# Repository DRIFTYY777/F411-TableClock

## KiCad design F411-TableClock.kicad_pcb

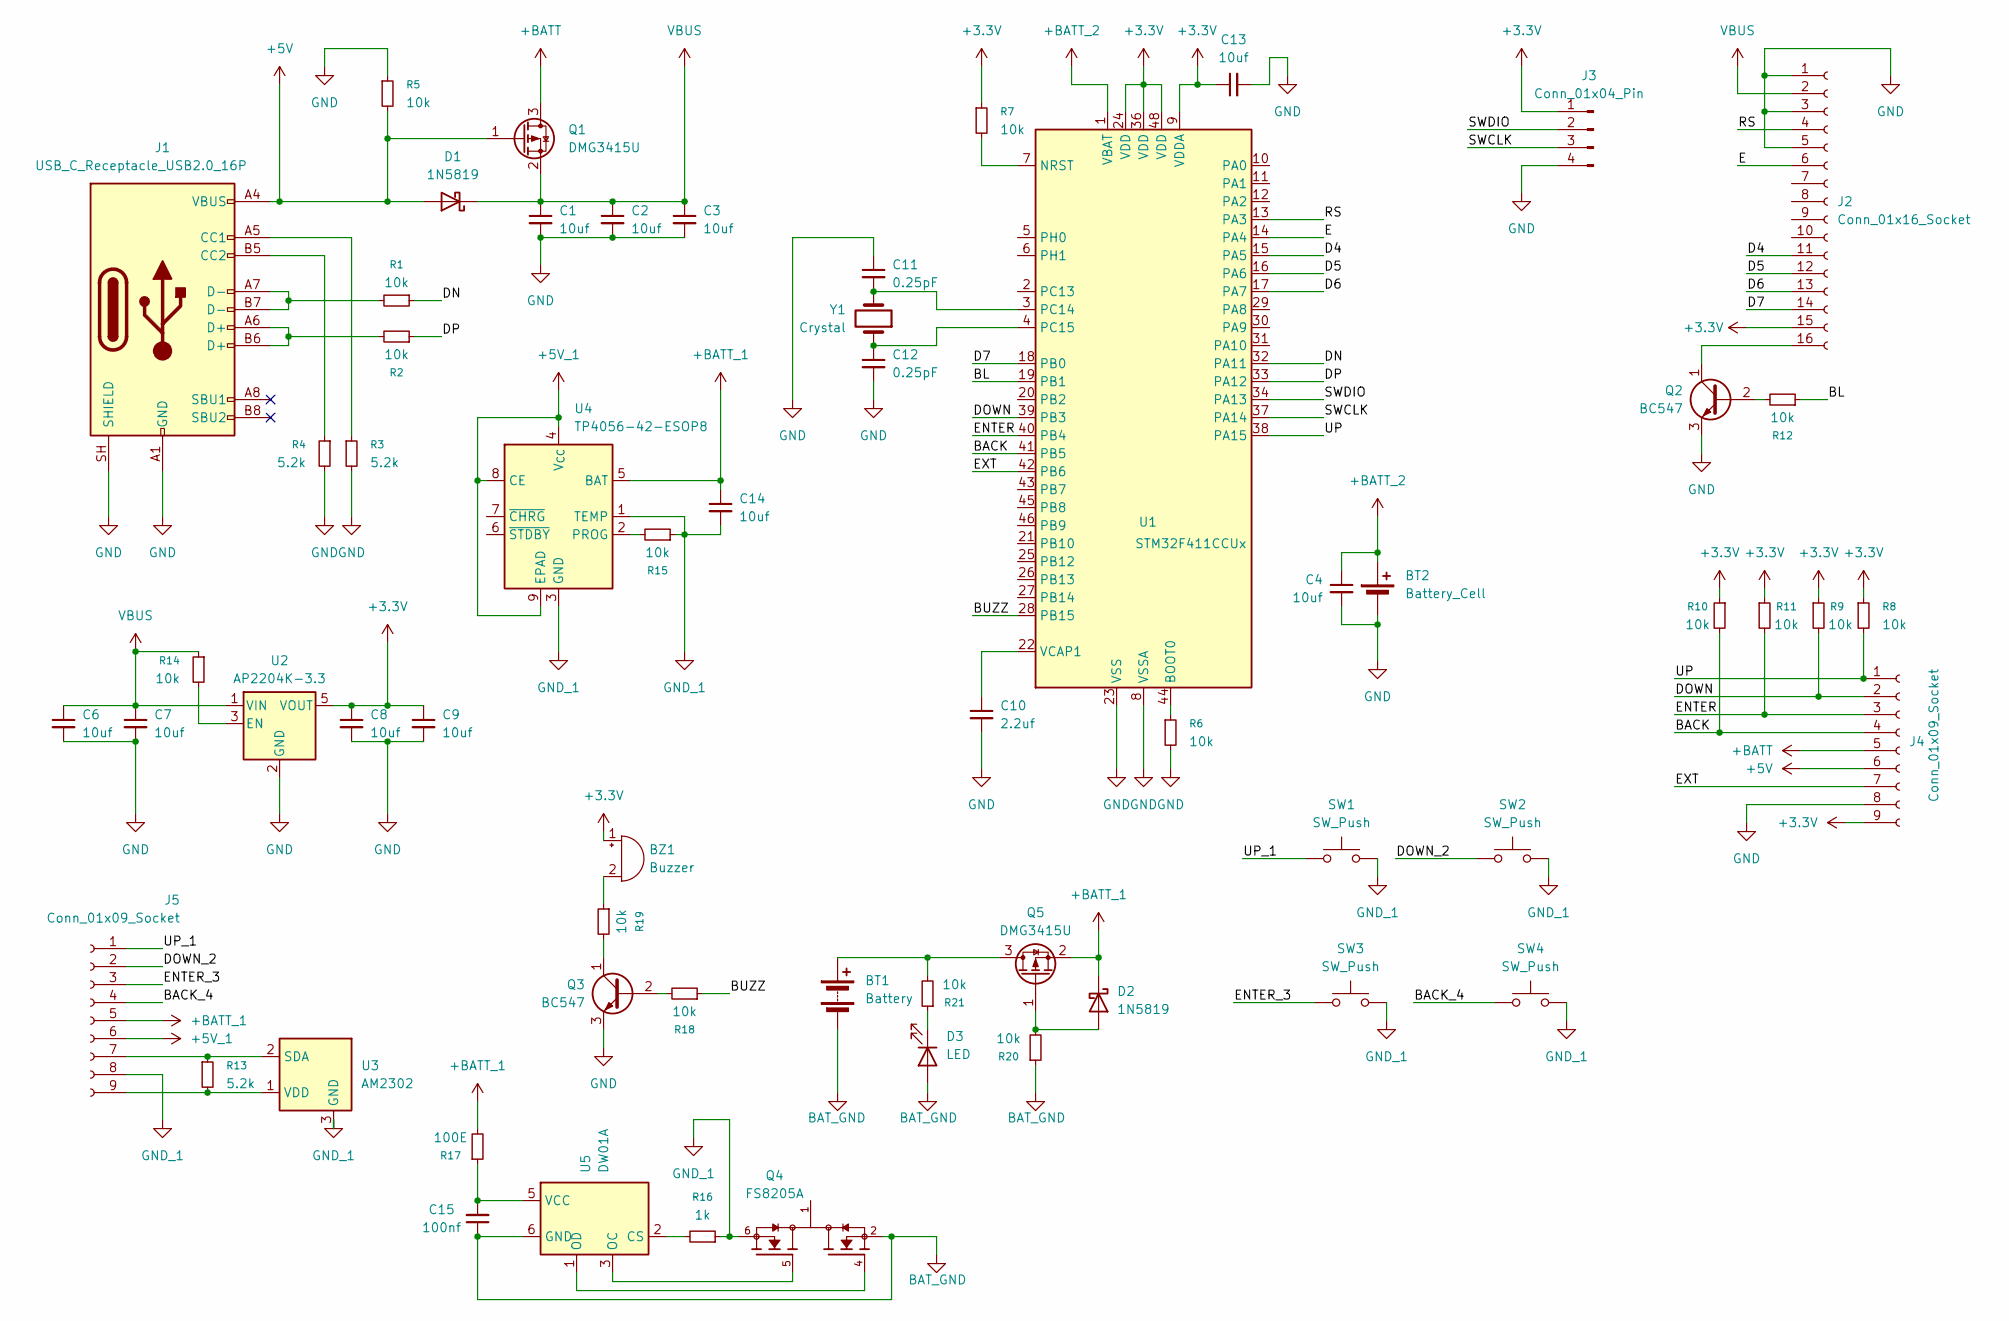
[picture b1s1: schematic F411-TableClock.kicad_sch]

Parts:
BT1: Battery; BatteryHolder_MPD_BK-18650-PC2
BT2: Battery_Cell; Battery_Panasonic_CR2032-HFN_Horizontal_CircularHoles
BZ1: Buzzer; Buzzer_12x9.5RM7.6
C1, C2, C3, C4, C6, C7, C8, C9, C13, C14: 10uf; C_0805_2012Metric
C10: 2.2uf; C_0805_2012Metric
C11, C12: 0.25pF; R_0805_2012Metric
C15: 100nf; C_0805_2012Metric
D1, D2: 1N5819; D_0805_2012Metric
D3: LED; LED_0805_2012Metric
J1: USB_C_Receptacle_USB2.0_16P; USB_C_Receptacle_GCT_USB4105-xx-A_16P_TopMnt_Horizontal
J2: Conn_01x16_Socket; PinSocket_1x16_P2.54mm_Vertical
J3: Conn_01x04_Pin; PinHeader_1x04_P2.54mm_Vertical
J4: Conn_01x09_Socket; PinSocket_1x09_P2.54mm_Vertical
J5: Conn_01x09_Socket; PinHeader_1x09_P2.54mm_Vertical
Q1, Q5: DMG3415U; SOT-23
Q2, Q3: BC547; TSOT-23
Q4: FS8205A; TSSOP-8_4.4x3mm_P0.65mm; PARTREV 1.7
R1, R2, R5, R6, R7, R8, R9, R10, R11, R12, R14, R15, R18, R19, R20, R21: 10k; R_0805_2012Metric
R3, R4, R13: 5.2k; R_0805_2012Metric
R16: 1k; R_0805_2012Metric
R17: 100E; R_0805_2012Metric
SW1, SW2, SW3, SW4: SW_Push; SW_SPST_TL3342
U1: STM32F411CCUx; QFN-48-1EP_7x7mm_P0.5mm_EP5.15x5.15mm
U2: AP2204K-3.3; SOT-23-5
U3: AM2302; ASAIR_AM2302_P2.54mm_Vertical
U4: TP4056-42-ESOP8; SOIC-8-1EP_3.9x4.9mm_P1.27mm_EP2.41x3.3mm_ThermalVias
U5: DW01A; SOT-23-6
Y1: Crystal; Crystal_AT310_D3.0mm_L10.0mm_Vertical

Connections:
+3.3V: BZ1.1 (+), C8.1, C9.1, C13.1, J2.15, J3.1, J4.9, R7.1, R8.1, R9.1, R10.1, R11.1, U1.9 (VDDA), U1.24 (VDD), U1.36 (VDD), U1.48 (VDD), U2.5 (VOUT)
+5V: D1.2 (A), J1.A4 (VBUS), J1.A9 (VBUS), J1.B4 (VBUS), J1.B9 (VBUS), J4.6, Q1.1 (G), R5.2
+5V_1: J5.6, U4.4 (V_{CC}), U4.8 (CE), U4.9 (EPAD)
+BATT: J4.5, Q1.3 (D)
+BATT_1: C14.1, D2.1 (K), J5.5, Q5.2 (S), R17.2, U4.5 (BAT)
+BATT_2: BT2.1 (+), C4.1, U1.1 (VBAT)
/BACK: J4.4, R10.2, U1.41 (PB5)
/BACK_4: J5.4, SW4.1
/BL: R12.1, U1.19 (PB1)
/BUZZ: R18.1, U1.28 (PB15)
/D4: J2.11, U1.15 (PA5)
/D5: J2.12, U1.16 (PA6)
/D6: J2.13, U1.17 (PA7)
/D7: J2.14, U1.18 (PB0)
/DN: R1.1, U1.32 (PA11)
/DOWN: J4.2, R9.2, U1.39 (PB3)
/DOWN_2: J5.2, SW2.1
/DP: R2.1, U1.33 (PA12)
/E: J2.6, U1.14 (PA4)
/ENTER: J4.3, R11.2, U1.40 (PB4)
/ENTER_3: J5.3, SW3.1
/EXT: J4.7, U1.42 (PB6)
/RS: J2.4, U1.13 (PA3)
/SWCLK: J3.3, U1.37 (PA14)
/SWDIO: J3.2, U1.34 (PA13)
/UP: J4.1, R8.2, U1.38 (PA15)
/UP_1: J5.1, SW1.1
BAT_GND: BT1.2 (-), C15.1, D3.2 (A), Q4.2, Q4.3, R20.1, U5.6 (GND)
GND: BT2.2 (-), C1.2, C2.2, C3.2, C4.2, C6.2, C7.2, C8.2, C9.2, C10.2, C11.1, C12.2, C13.2, J1.A1 (GND), J1.A12 (GND), J1.B1 (GND), J1.B12 (GND), J1.SH (SHIELD), J2.1, J2.3, J2.5, J3.4, J4.8, Q2.3 (E), Q3.3 (E), R3.2, R4.2, R5.1, R6.2, U1.8 (VSSA), U1.23 (VSS), U1.35 (VSS), U1.47 (VSS), U1.49 (VSS), U2.2 (GND)
GND_1: C14.2, J5.8, Q4.6, Q4.7, R15.1, R16.1, SW1.2, SW2.2, SW3.2, SW4.2, U3.3 (GND), U3.4 (GND), U4.1 (TEMP), U4.3 (GND)
unnamed: BT1.1 (+), Q5.3 (D), R21.2
unnamed: BZ1.2 (-), R19.1
unnamed: D2.2 (A), Q5.1 (G), R20.2
unnamed: D3.1 (K), R21.1
unnamed: J1.A5 (CC1), R3.1
unnamed: J1.B5 (CC2), R4.1
unnamed: J1.A6 (D+), J1.B6 (D+), R2.2
unnamed: J1.A7 (D-), J1.B7 (D-), R1.2
unnamed: J2.16, Q2.1 (C)
unnamed: J5.7, R13.1, U3.2 (SDA)
unnamed: J5.9, R13.2, U3.1 (VDD)
unnamed: Q2.2 (B), R12.2
unnamed: Q3.2 (B), R18.2
unnamed: Q3.1 (C), R19.2
unnamed: Q4.1, Q4.8
unnamed: R6.1, U1.44 (BOOT0)
unnamed: R7.2, U1.7 (NRST)
unnamed: C11.2, U1.3 (PC14), Y1.2
unnamed: C12.1, U1.4 (PC15), Y1.1
unnamed: C10.1, U1.22 (VCAP1)
unnamed: R14.2, U2.3 (EN)
unnamed: R15.2, U4.2 (PROG)
unnamed: R16.2, U5.2 (CS)
unnamed: Q4.5, U5.3 (OC)
unnamed: Q4.4, U5.1 (OD)
unnamed: C15.2, R17.1, U5.5 (VCC)
VBUS: C1.1, C2.1, C3.1, C6.1, C7.1, D1.1 (K), J2.2, Q1.2 (S), R14.1, U2.1 (VIN)

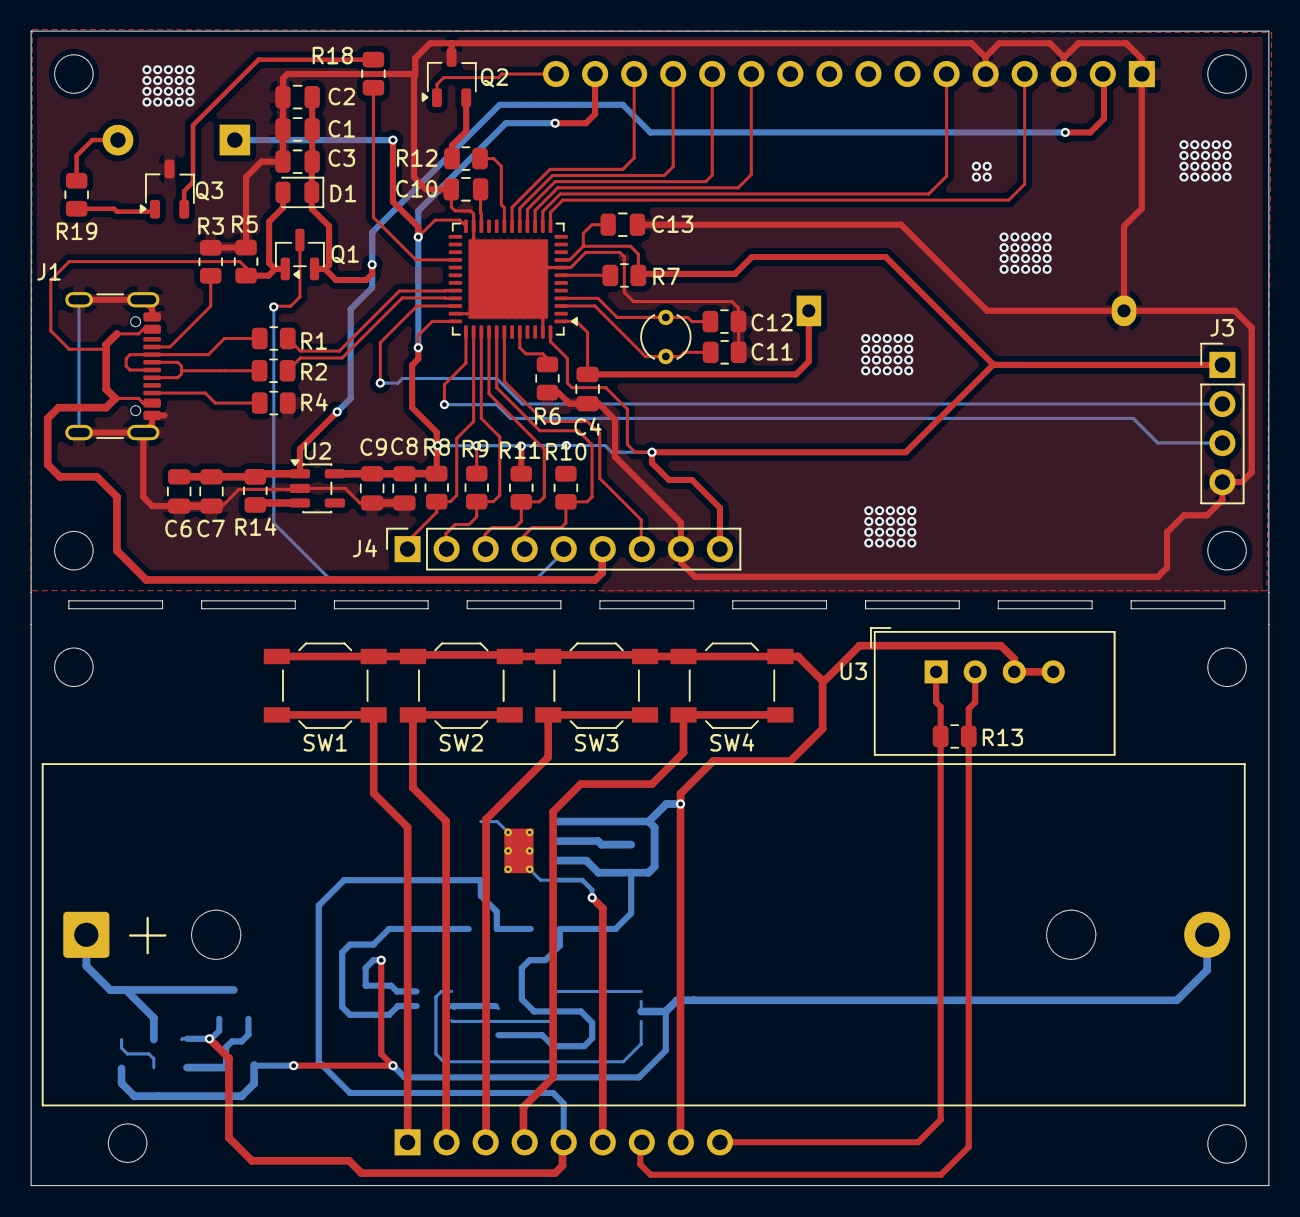
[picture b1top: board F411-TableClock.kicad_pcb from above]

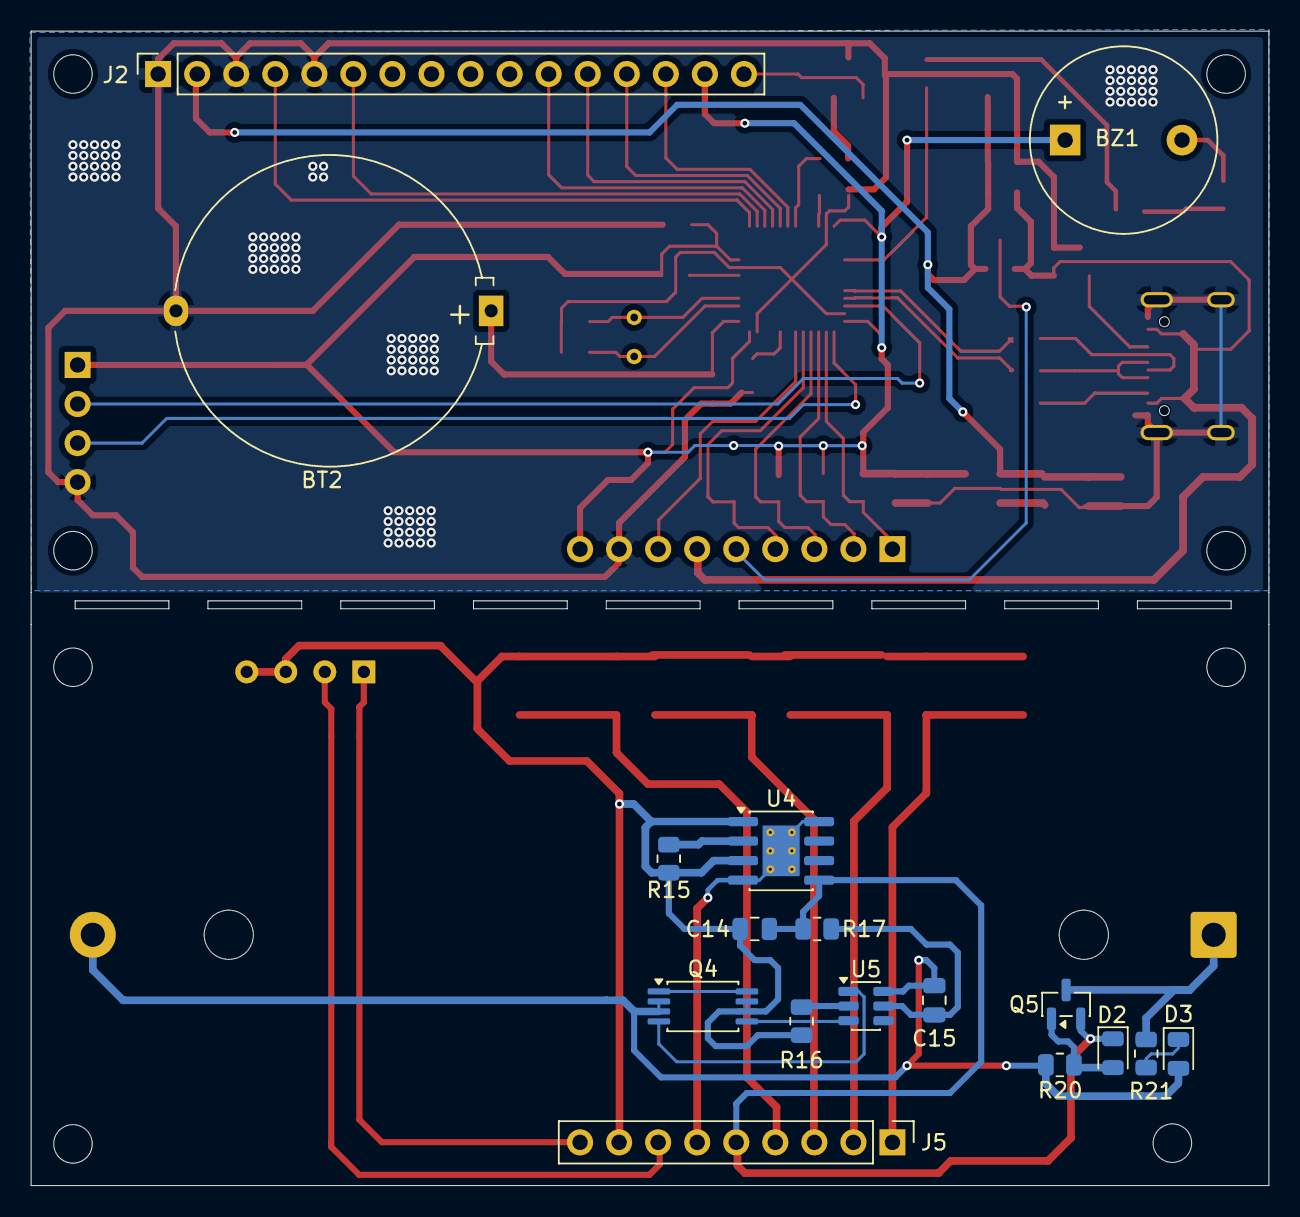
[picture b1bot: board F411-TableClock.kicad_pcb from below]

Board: 2 copper layers, 80.5 x 75.1 mm, 61 parts (17 on the bottom side), 57 nets.

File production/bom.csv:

Designator,Footprint,Quantity,Value,LCSC Part #
BT1,BatteryHolder_MPD_BK-18650-PC2,1,Battery,
BT2,Battery_Panasonic_CR2032-HFN_Horizontal_CircularHoles,1,Battery_Cell,
"C1, C13, C2, C3, C4, C5, C6, C7, C8, C9",0805,10,10uf,
C10,0805,1,2.2uf,
"C11, C12",0805,2,0.25pF,
D1,0805,1,1N5819,
J1,USB_C_Receptacle_GCT_USB4105-xx-A_16P_TopMnt_Horizontal,1,USB_C_Receptacle_USB2.0_16P,
J2,PinSocket_1x16_P2.54mm_Vertical,1,Conn_01x16_Socket,
J3,PinHeader_1x04_P2.54mm_Vertical,1,Conn_01x04_Pin,
J4,PinSocket_1x09_P2.54mm_Vertical,1,Conn_01x09_Socket,
J5,PinHeader_1x09_P2.54mm_Vertical,1,Conn_01x09_Socket,
Q1,SOT-23,1,DMG3415U,
Q2,TO-92L_Wide,1,BC547,
"R1, R10, R11, R12, R14, R2, R5, R6, R7, R8, R9",0805,11,10k,
"R13, R3, R4",0805,3,5.2k,
"SW1, SW2, SW3, SW4",SW_SPST_TL3342,4,SW_Push,
U1,QFN-48-1EP_7x7mm_P0.5mm_EP5.15x5.15mm,1,STM32F411CCUx,
U2,SOT-23-5,1,AP2204K-3.3,
U3,ASAIR_AM2302_P2.54mm_Vertical,1,AM2302,
Y1,Crystal_AT310_D3.0mm_L10.0mm_Vertical,1,Crystal,

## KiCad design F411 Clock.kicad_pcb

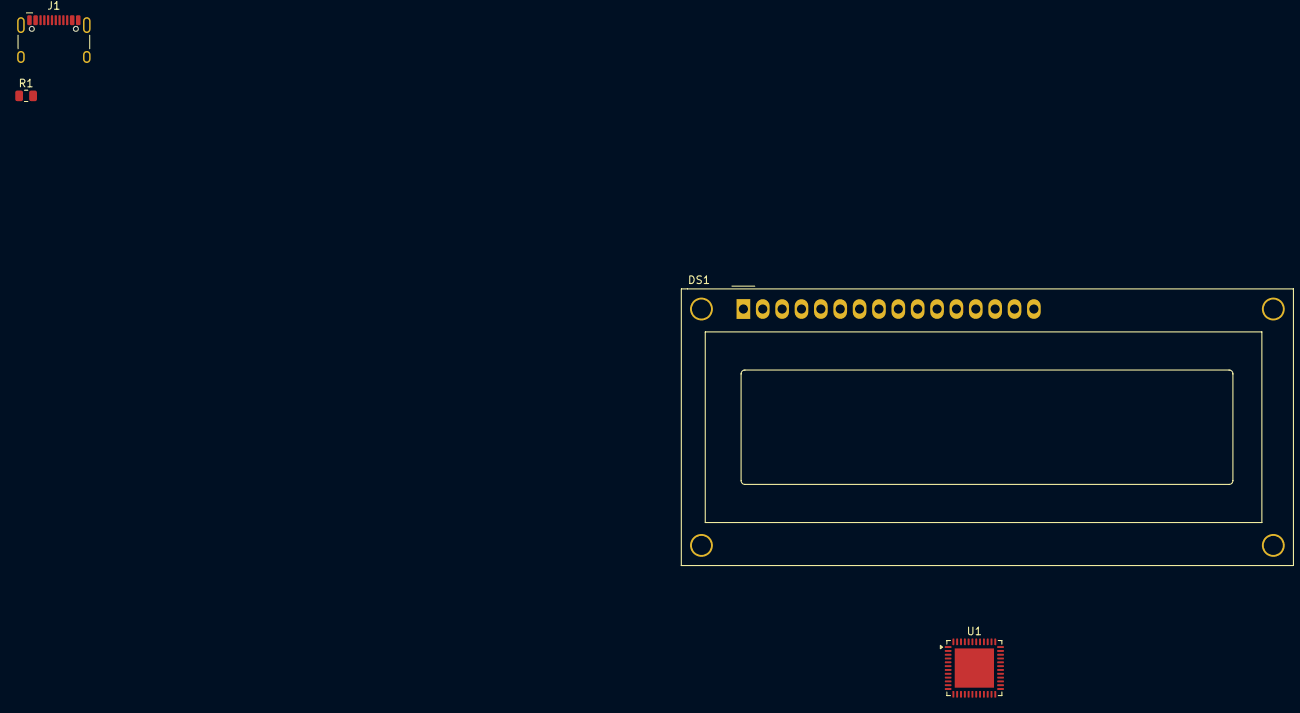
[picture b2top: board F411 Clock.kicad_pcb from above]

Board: 2 copper layers, 4 parts (0 on the bottom side), 5 nets, no tracks yet.

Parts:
DS1: WC1602A
J1: USB_C_Receptacle_USB2.0_16P; USB_C_Receptacle_HCTL_HC-TYPE-C-16P-01A
R1: R_Small; R_0805_2012Metric
U1: STM32F411CCUx; QFN-48-1EP_7x7mm_P0.5mm_EP5.15x5.15mm

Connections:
unnamed: J1.A6 (D+), J1.B6 (D+)
unnamed: J1.A7 (D-), J1.B7 (D-)
unnamed: J1.A1 (GND), J1.A12 (GND), J1.B1 (GND), J1.B12 (GND)
unnamed: J1.A4 (VBUS), J1.A9 (VBUS), J1.B4 (VBUS), J1.B9 (VBUS)
unnamed: U1.23 (VSS), U1.35 (VSS), U1.47 (VSS), U1.49 (VSS)

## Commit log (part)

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2026-04-01 Initial snapshot: 3 files changed F411 Clock.kicad_pcb 2/0/0 F411 Clock.kicad_pro 1/0/0 F411 Clock.kicad_sch 14/0/0
2026-04-01 SCH Save: 1 files changed F411 Clock.kicad_pro 5/0/1
2026-04-01 SCH Save: 4 files changed F411 Clock.kicad_prl 105/0/0 F411 Clock.kicad_pro 429/0/1 F411 Clock.kicad_sch 1893/0/3 ~F411 Clock.kicad_sch.lck 1/0/0
2026-04-01 PCB Save: 4 files changed F411 Clock.kicad_pcb 1692/0/2 F411 Clock.kicad_prl 22/0/2 F411 Clock.kicad_pro 216/0/0 ~F411 Clock.kicad_pcb.lck 1/0/0
2026-04-01 SCH Save: 2 files changed F411 Clock.kicad_pro 0/0/1 F411 Clock.kicad_sch 898/0/6
2026-04-01 SCH Save: 2 files changed F411 Clock.kicad_pro 0/0/1 F411 Clock.kicad_sch 223/0/0
2026-04-01 PCB Save: 1 files changed F411 Clock.kicad_pcb 644/0/0
2026-04-01 SCH Save: 3 files changed F411 Clock.kicad_prl 11/0/2 F411 Clock.kicad_pro 0/0/1 F411 Clock.kicad_sch 170/0/22
2026-04-01 SCH Save: 2 files changed F411 Clock.kicad_pro 0/0/1 F411 Clock.kicad_sch 461/0/21
2026-04-01 SCH Save: 2 files changed F411 Clock.kicad_pro 0/0/1 F411 Clock.kicad_sch 218/0/60
2026-04-01 SCH Save: 1 files changed F411 Clock.kicad_sch 40/0/0
2026-04-01 SCH Save: 2 files changed F411 Clock.kicad_pro 0/0/1 F411 Clock.kicad_sch 10/0/0
2026-04-01 SCH Save: 2 files changed F411 Clock.kicad_pro 0/0/1 F411 Clock.kicad_sch 1935/0/521
2026-04-01 SCH Save: 1 files changed F411 Clock.kicad_sch 0/0/174
2026-04-01 SCH Save: 2 files changed F411 Clock.kicad_pro 0/0/1 F411 Clock.kicad_sch 78/0/0
2026-04-01 SCH Save: 2 files changed F411 Clock.kicad_pro 0/0/1 F411 Clock.kicad_sch 324/0/0
2026-04-01 SCH Save: 1 files changed F411 Clock.kicad_sch 0/0/13
2026-04-01 SCH Save: 2 files changed F411 Clock.kicad_pro 0/0/1 F411 Clock.kicad_sch 473/0/0
2026-04-01 SCH Save: 2 files changed F411 Clock.kicad_pro 0/0/1 F411 Clock.kicad_sch 216/0/0
2026-04-01 PCB Save: 1 files changed F411 Clock.kicad_pcb 0/0/2
2026-04-01 Discard unsaved pcb changes
2026-04-01 Add .gitignore and update PCB footprints; remove unused files
2026-04-01 Close: 3 files changed F411 Clock.kicad_pcb 0/0/3 F411 Clock.kicad_prl 138/0/0 F411 Clock.kicad_pro 651/0/0
2026-04-01 SCH Save: 4 files changed F411 Clock.kicad_pro 0/0/1 F411 Clock.kicad_sch 484/0/0 ~F411 Clock.kicad_pro.lck 1/0/0 ~F411 Clock.kicad_sch.lck 1/0/0
2026-04-01 SCH Save: 2 files changed F411 Clock.kicad_pro 0/0/1 F411 Clock.kicad_sch 64/0/127
2026-04-01 SCH Save: 2 files changed F411 Clock.kicad_pro 0/0/1 F411 Clock.kicad_sch 1152/0/302
2026-04-01 SCH Save: 1 files changed F411 Clock.kicad_sch 0/0/124
2026-04-01 SCH Save: 2 files changed F411 Clock.kicad_pro 0/0/1 F411 Clock.kicad_sch 647/0/19
2026-04-01 SCH Save: 1 files changed F411 Clock.kicad_sch 0/0/10
2026-04-01 SCH Save: 1 files changed F411 Clock.kicad_sch 0/0/8
2026-04-01 SCH Save: 2 files changed F411 Clock.kicad_pro 0/0/1 F411 Clock.kicad_sch 900/0/46
2026-04-01 SCH Save: 5 files changed .gitignore 3/0/0 F411 Clock.kicad_pro 0/0/1 F411 Clock.kicad_sch 3247/0/1089 ~F411 Clock.kicad_pcb.lck 0/1/0 ~F411 Clock.kicad_pro.lck 1/0/0
2026-04-01 SCH Save: 2 files changed F411 Clock.kicad_pro 0/0/1 F411 Clock.kicad_sch 176/0/12
2026-04-01 SCH Save: 1 files changed F411 Clock.kicad_sch 0/0/23
2026-04-01 SCH Save: 2 files changed F411 Clock.kicad_pro 0/0/1 F411 Clock.kicad_sch 288/0/23
2026-04-01 SCH Save: 1 files changed F411 Clock.kicad_sch 0/0/1
2026-04-01 PCB Save: 2 files changed F411 Clock.kicad_pcb 6362/0/1538 ~F411 Clock.kicad_pcb.lck 1/0/0
2026-04-01 Batter Holder and Buttons
2026-04-18 chore: clean up code structure and remove unused code blocks
2026-04-22 DHT added F411 table clock
2026-04-24 Refactor code structure for improved readability and maintainability
